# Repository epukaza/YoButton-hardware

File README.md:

## YoButton hardware
Hardware for the Yo button, including primitive plastic model, uses an ESP8266 to handle the Wi-Fi, and and MSP430 to handle USB negotiation for 500 ma charging and power to enable long standby times. Code for the ESP and MSP uC's is currently private

Board made in Eagle, PDF file of the schematic is supplied in the repo, direct link [here](https://github.com/epukaza/YoButton-hardware/raw/master/schematic.pdf)

# Board images:

# Renders:

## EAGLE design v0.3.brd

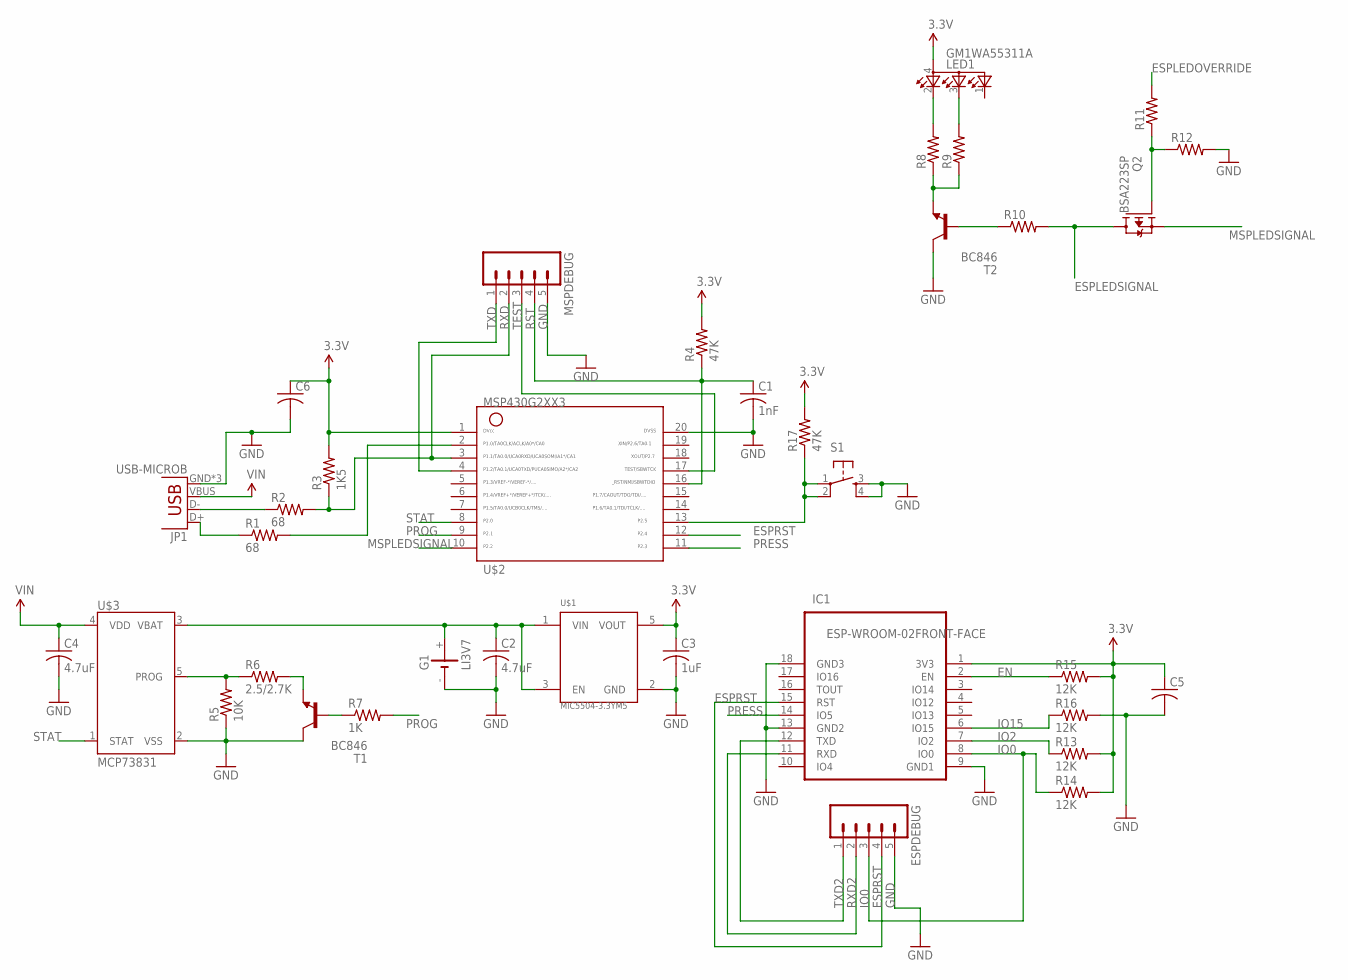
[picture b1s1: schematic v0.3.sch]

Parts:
C1: 1nF; C0603K
C2, C4: 4.7uF; C0603K
C3: 1uF; C0603K
C5, C6: C-USC0603K; C0603K
ESPDEBUG: M05LOCK; 1X05_LOCK
G1: LI3V7
IC1: ESP-WROOM-02FRONT-FACE; FRONT-FACE
JP1: USB-MICROB
LED1: GM1WA55311A
MSPDEBUG: M05LOCK; 1X05_LOCK
Q2: BSA223SP; SC75_INFINEON
R1, R2: 68; R0603
R3: 1K5; R0603
R4, R17: 47K; R0603
R5: 10K; R0603
R6: 2.5/2.7K; R0603
R7: 1K; R0603
R8, R9, R10, R11, R12: R-US_R0603; R0603
R13, R14, R15, R16: 12K; R0603
S1: TAC_SWITCHPTH; TACTILE-PTH
T1, T2: BC846; SOT23
U$1: MIC5504-3.3YM5; SOT23-5
U$2: G2XX3---PW20; PW20
U$3: MCP73831; SOT23-5

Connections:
3.3V: C3.1, C5.1, C6.1, IC1.1 (3V3), LED1.4 (A), R3.2, R4.2, R13.2, R14.2, R15.2, R17.2, U$1.5 (VOUT), U$2.1
EN: IC1.2 (EN), R15.1
ESPLEDOVERRIDE: R11.2
ESPLEDSIGNAL: Q2.2 (D), R10.2
ESPRST: ESPDEBUG.4, IC1.15 (RST), U$2.12
GND: C1.2, C2.2, C3.2, C4.2, C5.2, C6.2, ESPDEBUG.5, G1.-, IC1.9 (GND1), IC1.13 (GND2), IC1.18 (GND3), JP1.GND, JP1.MT1 (GND), JP1.MT2 (GND), MSPDEBUG.5, R5.1, R12.2, R16.2, S1.3, S1.4, T1.3 (C), T2.3 (C), U$1.2 (GND), U$2.20, U$3.2 (VSS)
IO0: ESPDEBUG.3, IC1.8 (IO0), R14.1
IO2: IC1.7 (IO2), R13.1
IO15: IC1.6 (IO15), R16.1
MSPLEDSIGNAL: Q2.3 (S), U$2.10
unnamed: R5.2, R6.1, U$3.5 (PROG)
unnamed: JP1.D+, R1.1
unnamed: JP1.D-, R2.1
unnamed: R1.2, U$2.2
unnamed: C2.1, G1.+, U$1.1 (VIN), U$1.3 (EN), U$3.3 (VBAT)
unnamed: R6.2, T1.2 (E)
unnamed: R7.1, T1.1 (B)
unnamed: R17.1, S1.1, S1.2, U$2.13
unnamed: LED1.2 (CRED), R8.2
unnamed: LED1.3 (CBLUE), R9.2
unnamed: R10.1, T2.1 (B)
unnamed: R8.1, R9.1, T2.2 (E)
unnamed: Q2.1 (G), R11.1, R12.1
PRESS: IC1.14 (IO5), U$2.11
PROG: R7.2, U$2.9
RST: C1.1, MSPDEBUG.4, R4.1, U$2.16
RXD: MSPDEBUG.2, R2.2, R3.1, U$2.3
RXD2: ESPDEBUG.2, IC1.11 (RXD)
STAT: U$2.8, U$3.1 (STAT)
TEST: MSPDEBUG.3, U$2.17
TXD: MSPDEBUG.1, U$2.4
TXD2: ESPDEBUG.1, IC1.12 (TXD)
VIN: C4.1, JP1.VBUS, U$3.4 (VDD)

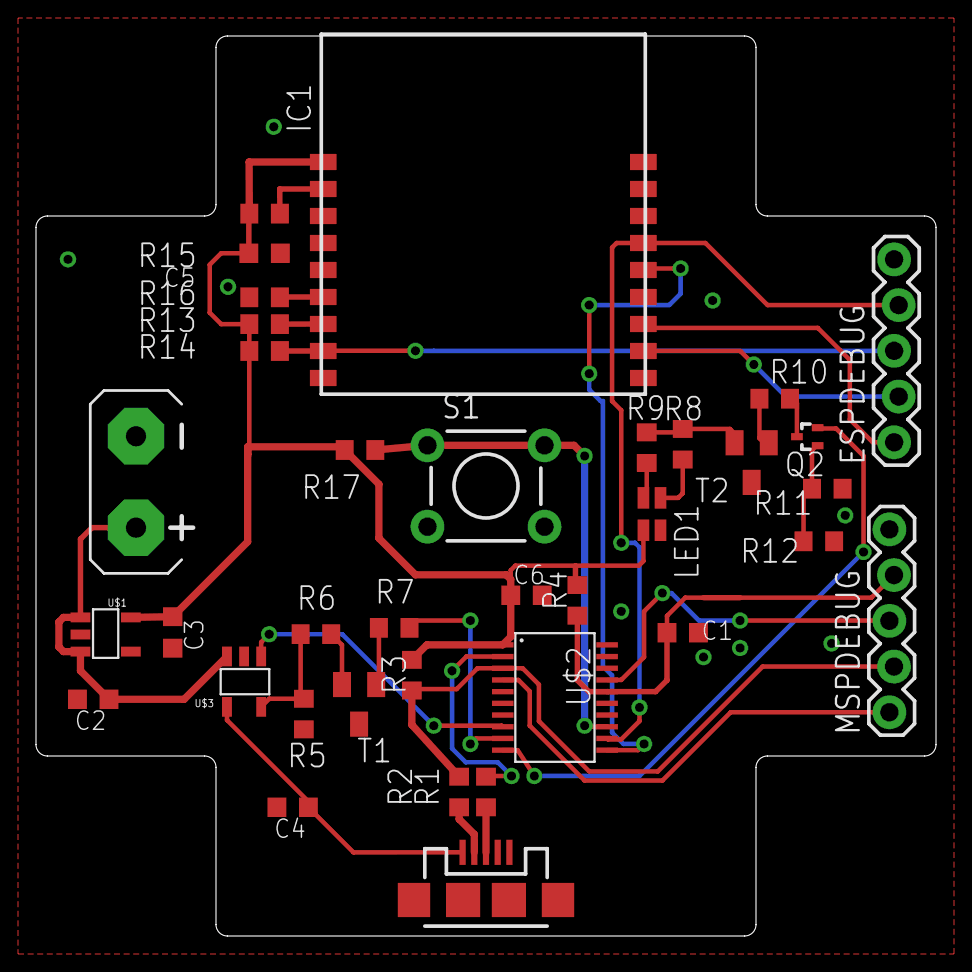
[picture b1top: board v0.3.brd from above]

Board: 2 copper layers, 50.0 x 50.0 mm, 36 parts (0 on the bottom side), 32 nets.

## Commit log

2016-04-20 Share project on github
2016-04-20 convert to jpg
2016-04-20 slight cosmetic update and added gitignore
2016-04-20 Removing all files in .gitignore
2016-04-20 add board images
2016-04-20 add schematic pdf
2019-06-08 fix simple typo

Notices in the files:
parts and their libraries:
SparkFun-Connectors: Licensing: Creative Commons ShareAlike 4.0 International - https://creativecommons.org/licenses/by-sa/4.0
